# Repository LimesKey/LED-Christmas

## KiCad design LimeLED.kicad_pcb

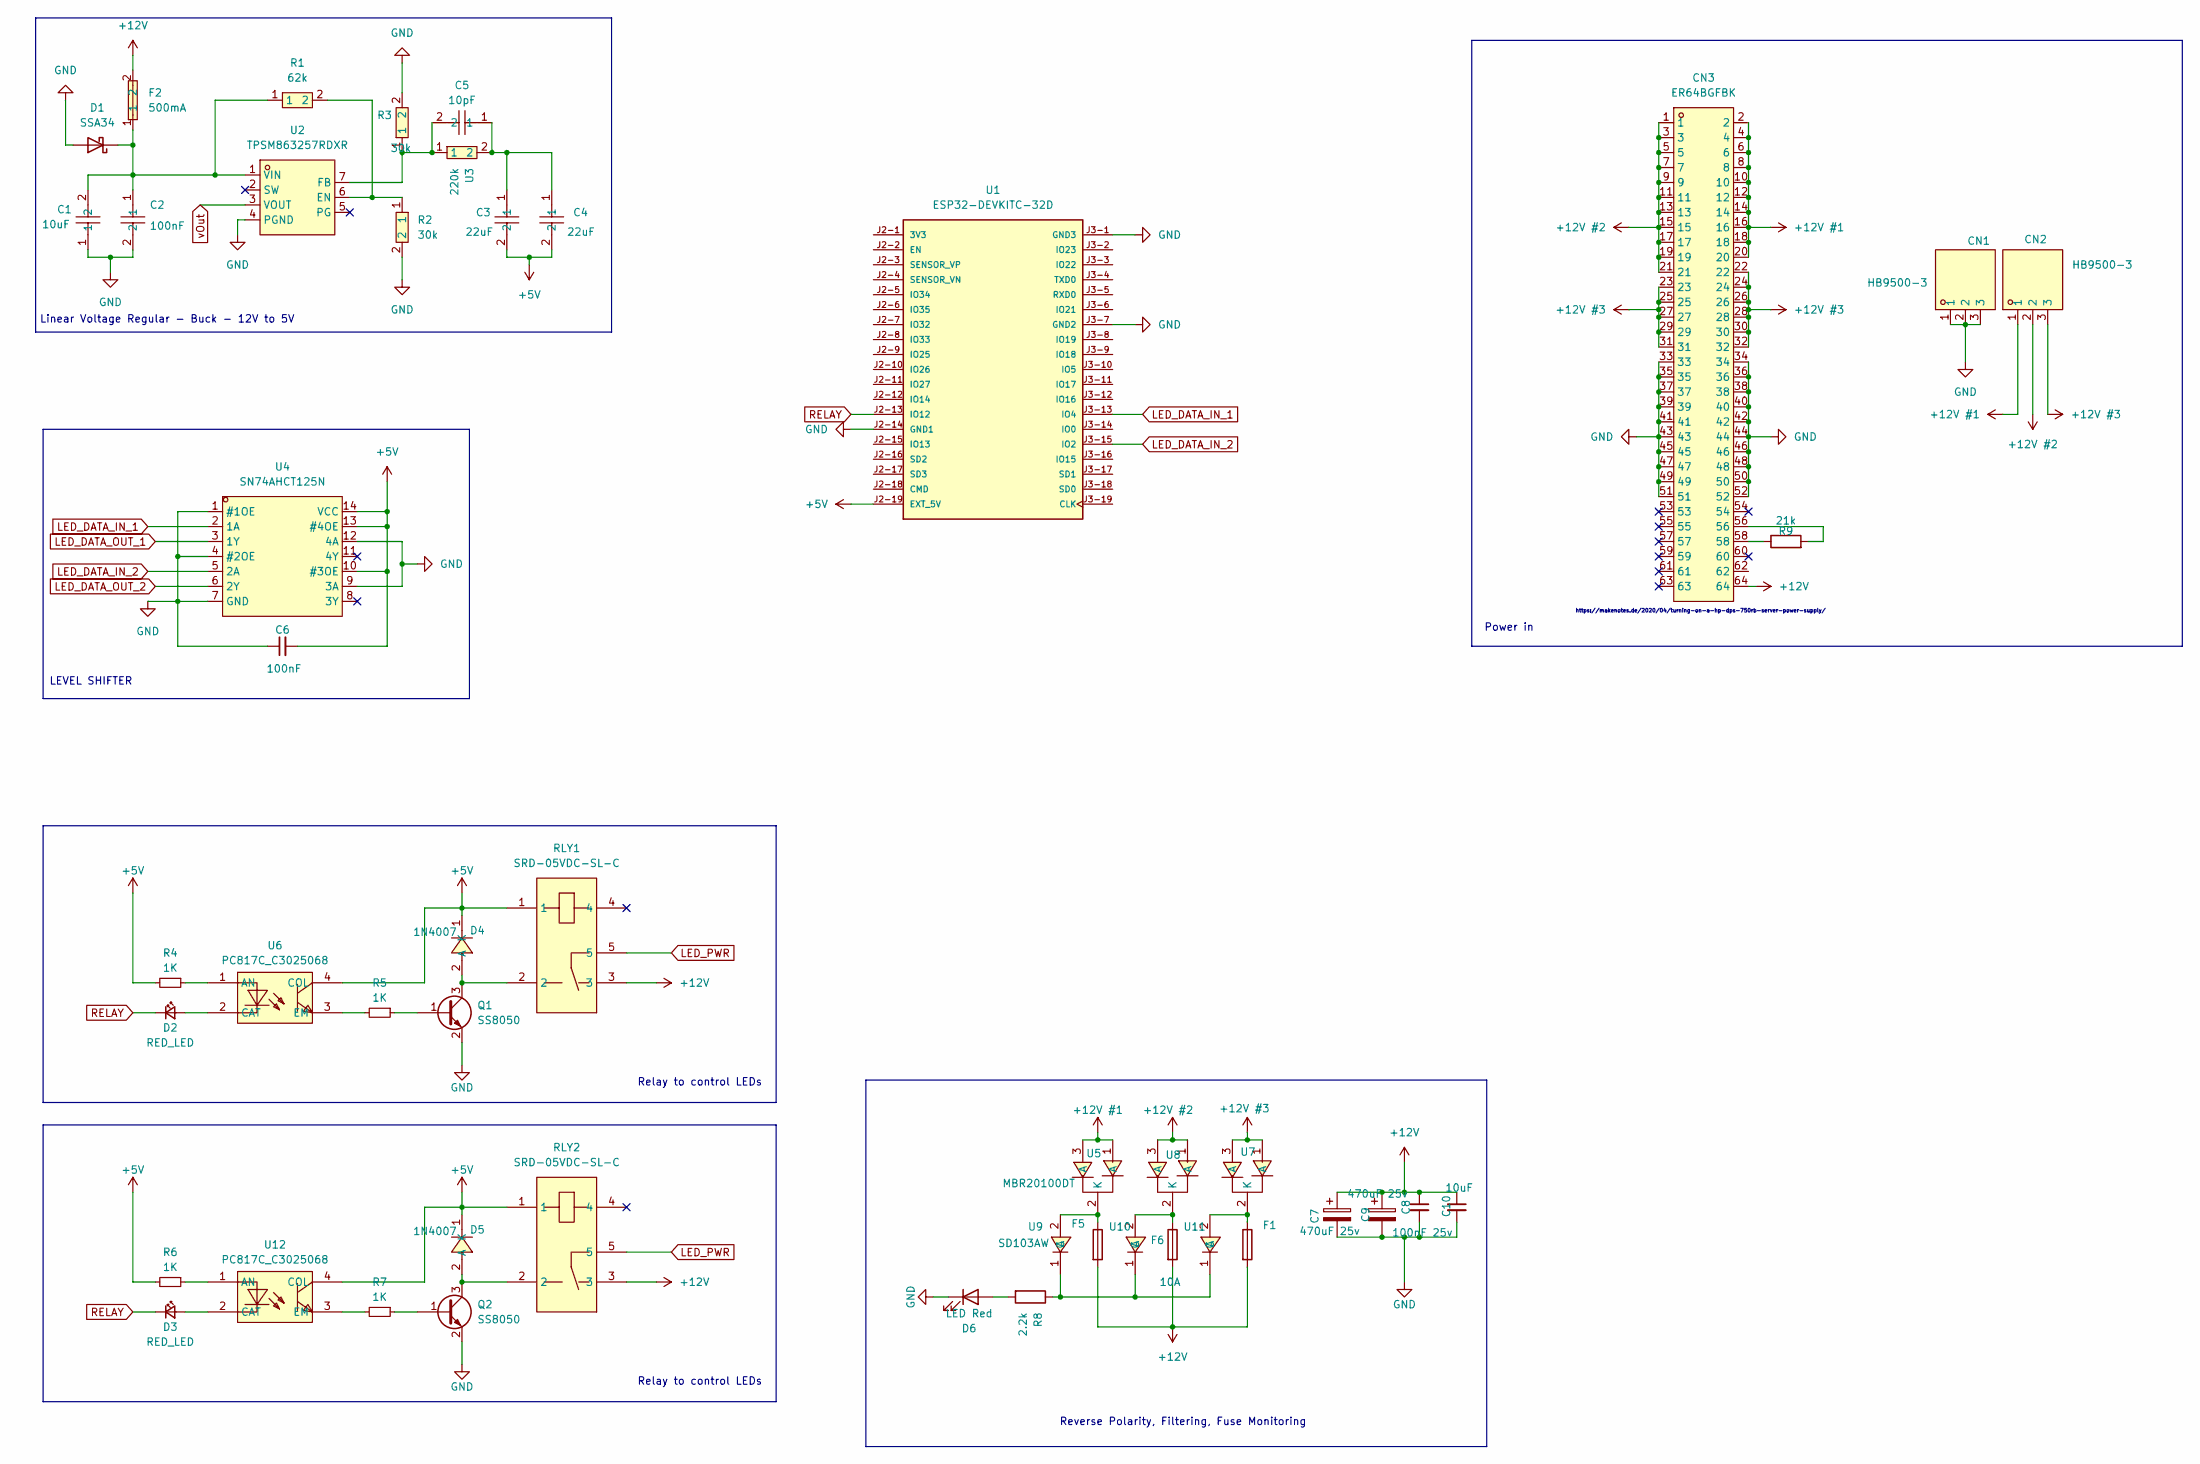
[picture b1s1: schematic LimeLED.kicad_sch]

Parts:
C1: 10uF; C0603; LCSC Part C1691
C2: 100nF; C0402; LCSC Part C6119799
C3, C4: 22uF; C0603; LCSC Part C159801
C5: 10pF; C0402; LCSC Part C713505
C6: 100nF; C_0402_1005Metric
C7, C9: 470uF 25v; CP_Radial_D8.0mm_P3.50mm; LCSC Part C2960234
C8: 100nF 25v; C_0402_1005Metric; LCSC Part C880603
C10: 10uF; C_0603_1608Metric; LCSC Part C466782
CN1, CN2: HB9500-3; CONN-TH_3P-P9.50_HB9500-9.5-3P; LCSC Part C162697
CN3: ER64BGFBK; CONN-TH_64P-P2.54_ER64BGFBK; LCSC Part C5173350
D1: SSA34; D_SMA; LCSC Part C5563753
D2, D3: RED_LED; LED_0805_2012Metric_Pad1.15x1.40mm_HandSolder
D4, D5: 1N4007; SMA_L4.3-W2.5-LS5.0-RD; LCSC Part C727081
D6: LED Red; LED_D3.0mm_Horizontal_O6.35mm_Z10.0mm
F1, F6: 10A; Ebay-Fuse-holder-04mmX15mm-black-auto-fuse-dingus
F2: 500mA; F1206; LCSC Part C170165
F5: 10A Medium Fuse Holder; Ebay-Fuse-holder-04mmX15mm-black-auto-fuse-dingus
Q1, Q2: SS8050; SOT-23; LCSC C431710
R1: 62k; R0402; LCSC Part C2929930
R2, R3: 30k; R0402; LCSC Part C163823
R4, R5, R6, R7: 1K; R_0402_1005Metric; LCSC Part C11702
R8: 2.2k; R_0603_1608Metric; LCSC Part C328351
R9: 21k; R_0603_1608Metric; LCSC Part C22956
RLY1, RLY2: SRD-05VDC-SL-C; RELAY-TH_SRD-XXVDC-XL-C; LCSC Part C35449
U1: ESP32-DEVKITC-32D; MODULE_ESP32-DEVKITC-32D; PARTREV V4
U2: TPSM863257RDXR; QFN-7_L4.0-W3.3_TPSM863257RDXR; LCSC Part C19190416
U3: 220k; R0402; LCSC Part C364970
U4: SN74AHCT125N; PDIP-14_L19.3-W6.4-P2.54-LS7.6-BL; LCSC Part C354152
U5, U7, U8: MBR20100DT; TO-252-2_L6.5-W6.1-P4.58-LS10.0-BL; LCSC Part C3011043
U6, U12: PC817C_C3025068; DIP-4_L4.6-W6.5-P2.54-LS7.6-BL; LCSC Part C3025068
U9, U10, U11: SD103AW; SOD-123_L2.8-W1.8-LS3.7-RD; LCSC Part C5345965

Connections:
+5V: C3.2, C4.2, C6.2, D4.1 (K), D5.1 (K), R4.2, R6.2, RLY1.1, RLY2.1, U1.J2-19 (EXT_5V), U4.10 (#3OE), U4.13 (#4OE), U4.14 (VCC), U6.4 (COL), U12.4 (COL)
+12V: C7.1, C8.1, C9.1, C10.1, CN3.64, F1.2, F2.2, F5.2, F6.2, RLY1.3, RLY2.3
+12V #1: CN2.1, CN3.2, CN3.4, CN3.6, CN3.8, CN3.10, CN3.12, CN3.14, CN3.16, CN3.18, CN3.20, U5.1 (A), U5.3 (A)
+12V #2: CN2.2, CN3.1, CN3.3, CN3.5, CN3.7, CN3.9, CN3.11, CN3.13, CN3.15, CN3.17, CN3.19, CN3.21, U8.1 (A), U8.3 (A)
+12V #3: CN2.3, CN3.22, CN3.23, CN3.24, CN3.25, CN3.26, CN3.27, CN3.28, CN3.29, CN3.30, CN3.31, CN3.32, U7.1 (A), U7.3 (A)
GND: C1.1, C2.2, C6.1, C7.2, C8.2, C9.2, C10.2, CN1.1, CN1.2, CN1.3, CN3.33, CN3.34, CN3.35, CN3.36, CN3.37, CN3.38, CN3.39, CN3.40, CN3.41, CN3.42, CN3.43, CN3.44, CN3.45, CN3.46, CN3.47, CN3.48, CN3.49, CN3.50, CN3.51, CN3.52, D1.2 (A), D6.1 (K), Q1.2 (E), Q2.2 (E), R2.2, R3.2, U1.J2-14 (GND1), U1.J3-1 (GND3), U1.J3-7 (GND2), U2.4 (PGND), U4.1 (#1OE), U4.4 (#2OE), U4.7 (GND), U4.9 (3A), U4.12 (4A)
LED_DATA_IN_1: U1.J3-13 (IO4), U4.2 (1A)
LED_DATA_IN_2: U1.J3-15 (IO2), U4.5 (2A)
LED_DATA_OUT_1: U4.3 (1Y)
LED_DATA_OUT_2: U4.6 (2Y)
LED_PWR: RLY1.5, RLY2.5
unnamed: C3.1, C4.1, C5.1, U3.2
unnamed: CN3.56, R9.2
unnamed: CN3.58, R9.1
unnamed: C1.2, C2.1, D1.1 (K), F2.1, R1.1, U2.1 (VIN)
unnamed: D2.2 (A), U6.2 (CAT)
unnamed: D3.2 (A), U12.2 (CAT)
unnamed: D4.2 (A), Q1.3 (C), RLY1.2
unnamed: D5.2 (A), Q2.3 (C), RLY2.2
unnamed: D6.2 (A), R8.2
unnamed: Q1.1 (B), R5.1
unnamed: Q2.1 (B), R7.1
unnamed: R1.2, R2.1, U2.6 (EN)
unnamed: C5.2, R3.1, U2.7 (FB), U3.1
unnamed: F5.1, U5.2 (K), U9.2 (A)
unnamed: R4.1, U6.1 (AN)
unnamed: R5.2, U6.3 (EM)
unnamed: F6.1, U8.2 (K), U10.2 (A)
unnamed: R8.1, U9.1 (C), U10.1 (C), U11.1 (C)
unnamed: F1.1, U7.2 (K), U11.2 (A)
unnamed: R6.1, U12.1 (AN)
unnamed: R7.2, U12.3 (EM)
RELAY: D2.1 (K), D3.1 (K), U1.J2-13 (IO12)
vOut: U2.3 (VOUT)

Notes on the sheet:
Relay to control LEDs
https://makenotes.de/2020/04/turning-on-a-hp-dps-750rb-server-power-supply/
LEVEL SHIFTER
Linear Voltage Regular - Buck - 12V to 5V
Power in
Reverse Polarity, Filtering, Fuse Monitoring

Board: 2 copper layers, 48 parts (0 on the bottom side), 31 nets, no tracks yet.

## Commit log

2024-08-19 add files
2024-08-19 add input protection and plotted schematic
2024-08-19 wire connections
2024-08-19 plot schematic
2024-08-20 add relay
2024-08-20 add 64p PSU connector
2024-08-20 finish input power connector
